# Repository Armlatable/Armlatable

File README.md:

# Armlatable

## 構成

- **PC**: 高度な制御・コーディネーション (Python)
- **Raspberry Pi Pico**: リアルタイムDCモーター制御 (C++/Arduino)
- **PC-Pico通信**: シリアル通信による指令・ステータス交換

## 1. ハードウェア準備

1. **電源供給**
    - ブレッドボードの電源ラインに DC電源 (約 12V ~ 15V) を供給する。

2. **PC接続**
    - **Pico**: USBケーブルでPCに接続する。
    - **U2D2 (Dynamixel)**: USBケーブルでPCに接続する。

## 2. ソフトウェア準備

ターミナルで本ディレクトリ (`Armlatable`) に移動し、以下の手順でセットアップを行います。

### 2.1 依存ライブラリのインストール
Pythonの依存ライブラリをインストールします（仮想環境 `venv` が作成されます）。
```bash
make install
```

### 2.2 ポートの自動検出と設定
デバイス（U2D2, R4/Pico）をPCに接続した状態で、以下のコマンドを実行します。
```bash
make setup
```
これにより、シリアルポートが自動検出され、ルートディレクトリの `config.yaml` が更新されます。

### 2.3 ファームウェアの書き込み (必要な場合のみ)
Arduino R4 WiFi または Raspberry Pi Pico にファームウェアを書き込みます。
```bash
# R4 WiFi の場合
arduino-cli compile --fqbn arduino:renesas_uno:unor4wifi firmware/r4_motor_driver/r4_motor_driver.ino
arduino-cli upload -p <PORT> --fqbn arduino:renesas_uno:unor4wifi firmware/r4_motor_driver/r4_motor_driver.ino
```

## 3. 設定の確認

ルートディレクトリの `config.yaml` で、ハードウェア構成に合わせて設定を調整できます。

```yaml
serial:
  motor_driver_type: "r4" # "r4" または "pico"
```

## 4. 実行

### 4.1 キーボード操作モード (推奨)

```bash
make keyboard
```

#### 操作方法
| キー | 動作 |
|------|------|
| `0` | **すべてのDynamixelを選択** |
| `1`, `2`, `3` | 個別のDynamixel IDを選択 |
| `a` / `d` | 選択中のDynamixelを増減 |
| `w` / `s` | DCモーター PWM +/- 50 |
| `x` | DCモーター 停止 |
| `e` / `r` | モーターの有効化 / 無効化 (Torque/STBY) |
| `m` | Dynamixelモード切替 (Position ↔ Velocity) |
| `Space` | 全停止 |
| `q` | 終了 |

### 4.2 自動テストモード

```bash
make test
```

## 5. その他

- **トラブルシューティング**
    - **ポートが検出されない**: `make setup` で検出されない場合は、`config.yaml` を手動で編集してください。
    - **Resource busy**: 他のシリアルモニタを閉じてください。

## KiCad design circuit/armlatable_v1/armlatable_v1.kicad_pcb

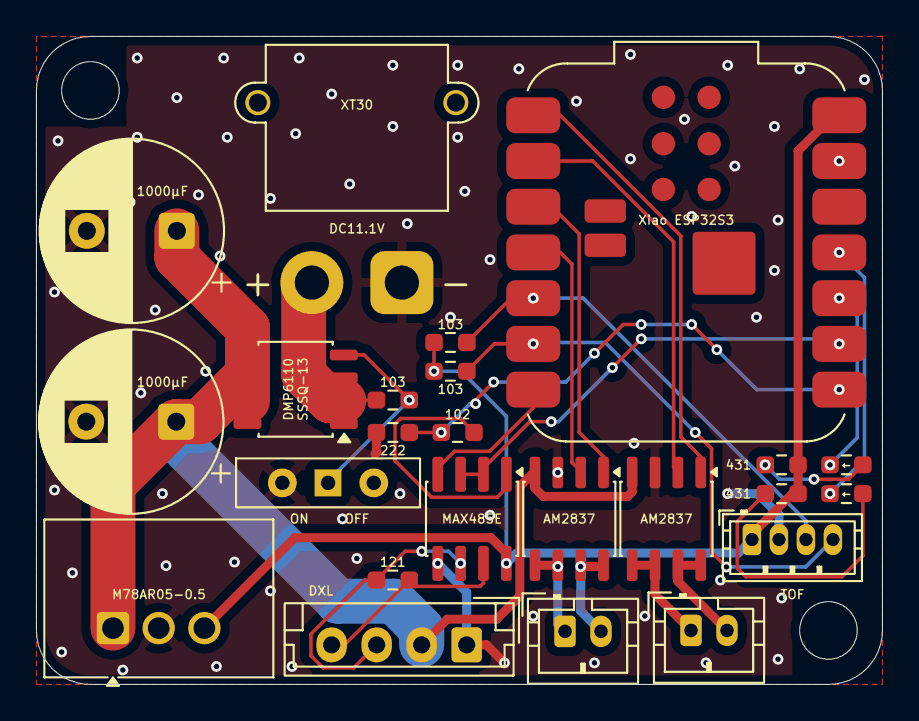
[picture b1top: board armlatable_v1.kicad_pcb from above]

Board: 2 copper layers, 47.0 x 36.0 mm, 24 parts (0 on the bottom side), 25 nets.

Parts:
102: 1kΩ; R_0603_1608Metric_Pad0.98x0.95mm_HandSolder
103, 103#2: 10kΩ; R_0603_1608Metric_Pad0.98x0.95mm_HandSolder
121: 120Ω; R_0603_1608Metric_Pad0.98x0.95mm_HandSolder
AM2837: SO-8_3.9x4.9mm_P1.27mm
C1, C2: 1000μF; CP_Radial_D10.0mm_P5.00mm
D1, D2: LED; R_0603_1608Metric_Pad0.98x0.95mm_HandSolder
DMP6110: Q_Dual_PMOS_S1G1S2G2D2D2D1D1; SSOP-8_3.9x5.05mm_P1.27mm
J2: Xiao ESP32S3; MCU_Seeed_ESP32C3
J3: DXL; JST_EH_B4B-EH-A_1x04_P2.50mm_Vertical
J4: Conn_01x04_Socket; JST_ZH_B4B-ZR_1x04_P1.50mm_Vertical
J6, J7: Conn_01x02_Socket; JST_PH_B2B-PH-K_1x02_P2.00mm_Vertical
M78AR05-0.5: TSR0.5-2450; Converter_DCDC_TRACO_TSR0.5-24xx_TSR0.5-24xxx_THT
ON: SW_SPDT; SW_Slide-03_Wuerth-WS-SLTV_10x2.5x6.4_P2.54mm
R1: 103; R_0603_1608Metric_Pad0.98x0.95mm_HandSolder
R3: 2.2kΩ; R_0603_1608Metric_Pad0.98x0.95mm_HandSolder
R7, R8: 430Ω; R_0603_1608Metric_Pad0.98x0.95mm_HandSolder
U2: MAX485E; SOIC-8_3.9x4.9mm_P1.27mm
U6: SO-8_3.9x4.9mm_P1.27mm
XT30: Conn_01x02_Pin; AMASS_XT30PW-M_1x02_P2.50mm_Horizontal

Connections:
+5V: 103.2, 103#2.1, J2.14, J4.1, M78AR05-0.5.3 (Vout), R7.2, R8.2, U2.8 (VCC)
+12V: AM2837.4 (VCC), C1.1, C2.1, DMP6110.7 (D), DMP6110.8 (D), J3.2, M78AR05-0.5.1 (Vin), U6.4 (VCC)
GND: AM2837.3 (GND), C1.2, C2.2, J2.13, J3.1, J4.2, M78AR05-0.5.2 (GND), ON.2 (B), R3.2, U2.5 (GND), U6.3 (GND), XT30.2
MD1INA: AM2837.1 (IN_A), J2.3
MD1INB: AM2837.2 (IN_B), J2.4
MD2INA: J2.1, U6.1 (IN_A)
MD2INB: J2.2, U6.2 (IN_B)
unnamed: D1.2 (A), R7.1
unnamed: D1.1 (K), J2.11
unnamed: D2.2 (A), R8.1
unnamed: D2.1 (K), J2.10
unnamed: DMP6110.1 (S), R1.2, XT30.1
unnamed: 121.1, J3.3, U2.6 (A)
unnamed: 121.2, J3.4, U2.7 (B)
unnamed: AM2837.7 (OUT_A), AM2837.8 (OUT_A), J6.1
unnamed: AM2837.5 (OUT_B), AM2837.6 (OUT_B), J6.2
unnamed: J7.1, U6.7 (OUT_A), U6.8 (OUT_A)
unnamed: J7.2, U6.5 (OUT_B), U6.6 (OUT_B)
unnamed: DMP6110.2 (G), ON.1 (A), R1.1
unnamed: 102.1, U2.1 (RO)
RDE: J2.9, U2.2 (~RE), U2.3 (DE)
RX: 102.2, J2.8, R3.1
SCL: 103#2.2, J2.6, J4.4
SDA: 103.1, J2.5, J4.3
TX: J2.7, U2.4 (DI)

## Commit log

2025-12-22 feat: dc_motor, dynamixelの制御コードを実装
2025-12-25 feat: dc_motor, dynamixelの制御コードを実装 (#2)
2026-01-15 feat: keyboard操作を追加
2026-01-15 Feat/proto control (#3)
    * feat: dc_motor, dynamixelの制御コードを実装
    * feat: keyboard操作を追加
2026-01-21 feat: proto_r4_wifiの追加、既存コードの整理
2026-01-21 feat: ファームウェア更新を最適化
2026-02-01 Add armlatable main pcb
2026-02-01 Modify silks
2026-02-02 feat: espをdongleとして使用したr4_wifiとの通信を実装
2026-02-08 feat: 動作確認用のコードを追加
2026-02-08 feat: outdatedを複数動作に対応
2026-02-08 feat: dynamixelの複数動作に対応
2026-02-08 feat: dcmotor_driverを複数動作に対応, r4へ
2026-02-08 feat: make installをwslに対応
2026-02-08 feat: usb_pathの自動確認を追加
2026-02-08 fix: wslのバグ抑制
2026-02-26 fix: Modify circuit
2026-03-07 docs: 構成図の追加
2026-03-07 docs: 構成図にarduino_unoを追加
